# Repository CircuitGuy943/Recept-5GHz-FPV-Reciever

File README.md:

I happened to have a 4.3" TFT display left over from dissassembling my old screen from my Ender 3 and I also had an ongoing project of a flight controller, with FPV functionality and I had an amazing idea, I present to you:

# **Recept!**

Recept is a 5.8GHz video signal reciever board running with an RX5808 as the reciever module and the combined power of an RP2040 and TW8819 decoder chip to quickly decode and output the video signal to a parallel RGB interface (3x8, 40 pin) for a generic 4.3" TFT display. It runs primarilly off of a fully integrated LiPo battery of dimensions and size 903759 / 2500mAh but it also provides the possibily of running off of USB C both for general use or charging the battery automatically using the built in BQ21088 charging chip from TI.

Power the backlight for the display there is an MT3608 24V boost converter paired with another buck/boost converter for the generic 5V rail (LDO wasn't suitable as the RX module power draw is quite high). However for the 1.8V and 3.3V rails, simple LD1117s were used for their low ripple, stable output and low power requirements of the TW8819 and RP2040 ICs. The PCB comes in the preferable dimensions for mounting a generic 4.3" TFT on the back with mounting points for a metal case that also came with my display. It also includes the main power switch (everything but charging) mounted next to the USB C port on the bottom of the board. On the left side you will also find the SMA connector for the 5.8GHz antenna and 8 LEDs, these LEDs are directly controlled by the RP2040 in response to the RSSI signal from the reciever, to give you an easy indication of the signal strength. Besides that there are also several power LEDs and GPIO LED on the other side of the board for general power and functionality debugging in addition to headers near to the SMA connector for more GPIOs/Power/RP2040 debugging. The board also has a keepout zone design to allow double sided tape mounting of the 903759 LiPo battery (on the other side of the display) where it can be easilly soldered to the pads for the battery connection.

There is also a really sleekly designed friction fit case (your mileage may vary with tolerances) designed to house the TFT display and battery mounted on the PCB all in one. It's designed to be easy to print, no supports and pretty much as simple as it gets to assemble. And if that wasn't enough for your preferences of beautiful design, a silkscreen pattern also embosses the board on both sides (although what use this is as you can't even see it in the case, don't ask me) to give a super cool aesthetic.

To use this you simply need the PCB, the display is attached to it using the metal bracket/casing it came in and the battery can either be stuck on with double sided tape or if you're putting it in the case it can even be left loose as it'll be contained. The device then fits into the bottom section of the case and the top section then just simply friction fits over it and sits in place. The configuration code can then bu uploaded using Arduino IDE via the USB C cable onto the RP2040 to configure the TW8819 and allow it to show video on the TFT display.

## Features:
- USB C power supply programming port for the RP2040
- 1s LiPo integration with built in charging
- 4.3" 40 pin TFT display support
- 5.8GHz video band
- Channel switch ability
- RSSI support
- No screw assembly

## PCB
This is the PCB, with L1 to L4 Layers, silkscreen for both layers and an all layers view

And here is the schematic

## Case and 3D renders
Here are also some 3D renders done in fusion to show off the case and it's functionality :)

And last but not least this is a render of the PCB itself:

## Firmware Overview
I've included some basic firmware (**untested**) that should get the TFT display working out of the box with a quick upload from arduino IDE

## BOM:
The BOM list for the actual PCB components is in the BOM folder section and here is also a BOM list for all the other components I plan to buy for this:

- PCB             $198.94		
- Antenna         $7.77      https://www.aliexpress.com/item/1005006153683653.html		
- 90 degree SMA   $4.51      https://www.aliexpress.com/item/1005005665998117.html						
- RX5808 module   $33.54     https://www.ebay.co.uk/itm/264574341923						                (This module is not cheaper on AliExpress)
- Battery         $9.39      https://www.ebay.co.uk/itm/396305473532?var=665862385939						(I don't feel safe buying batteries off Ali)
											
Total			      $246.38

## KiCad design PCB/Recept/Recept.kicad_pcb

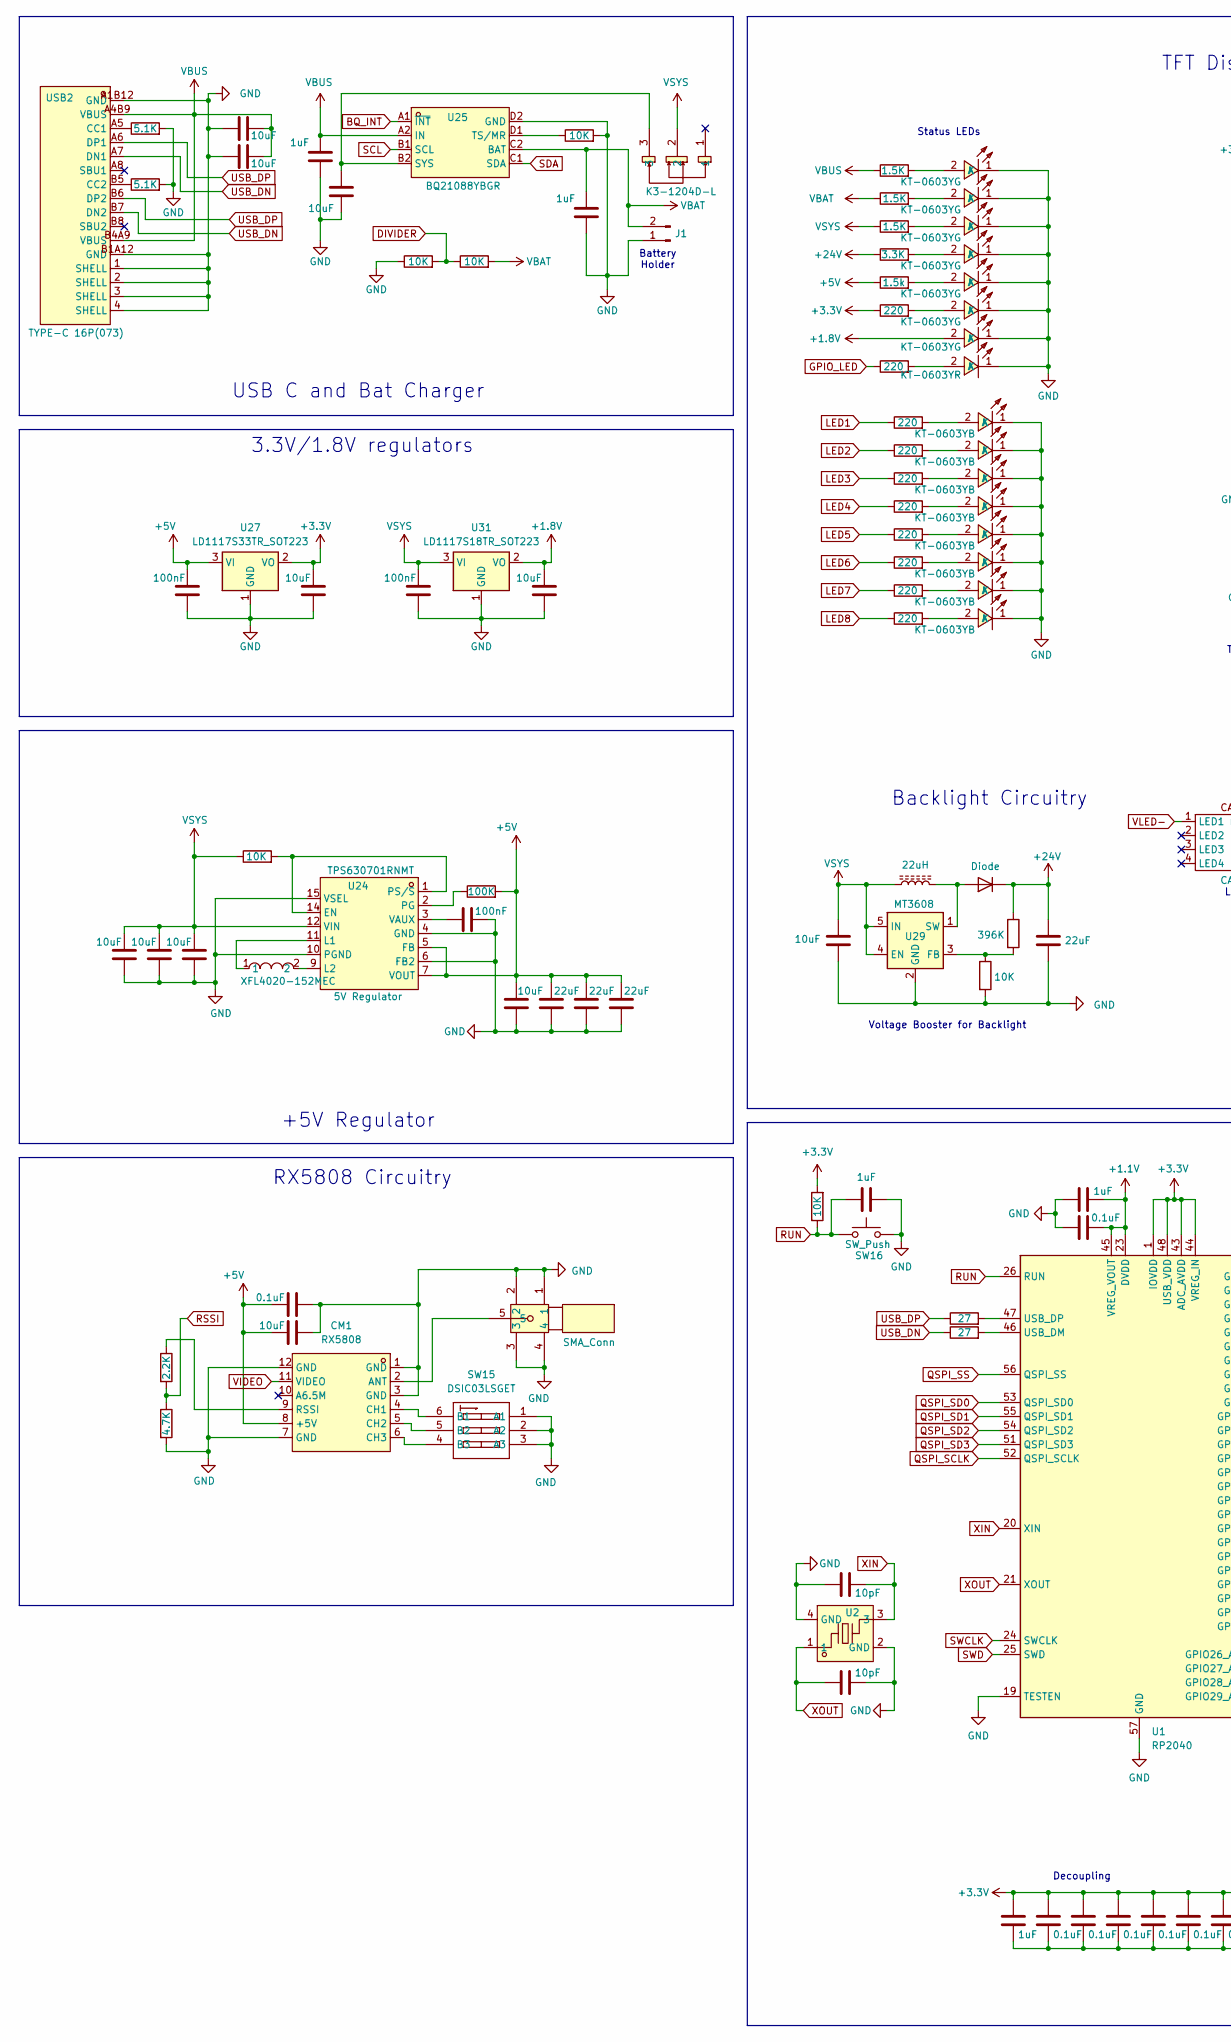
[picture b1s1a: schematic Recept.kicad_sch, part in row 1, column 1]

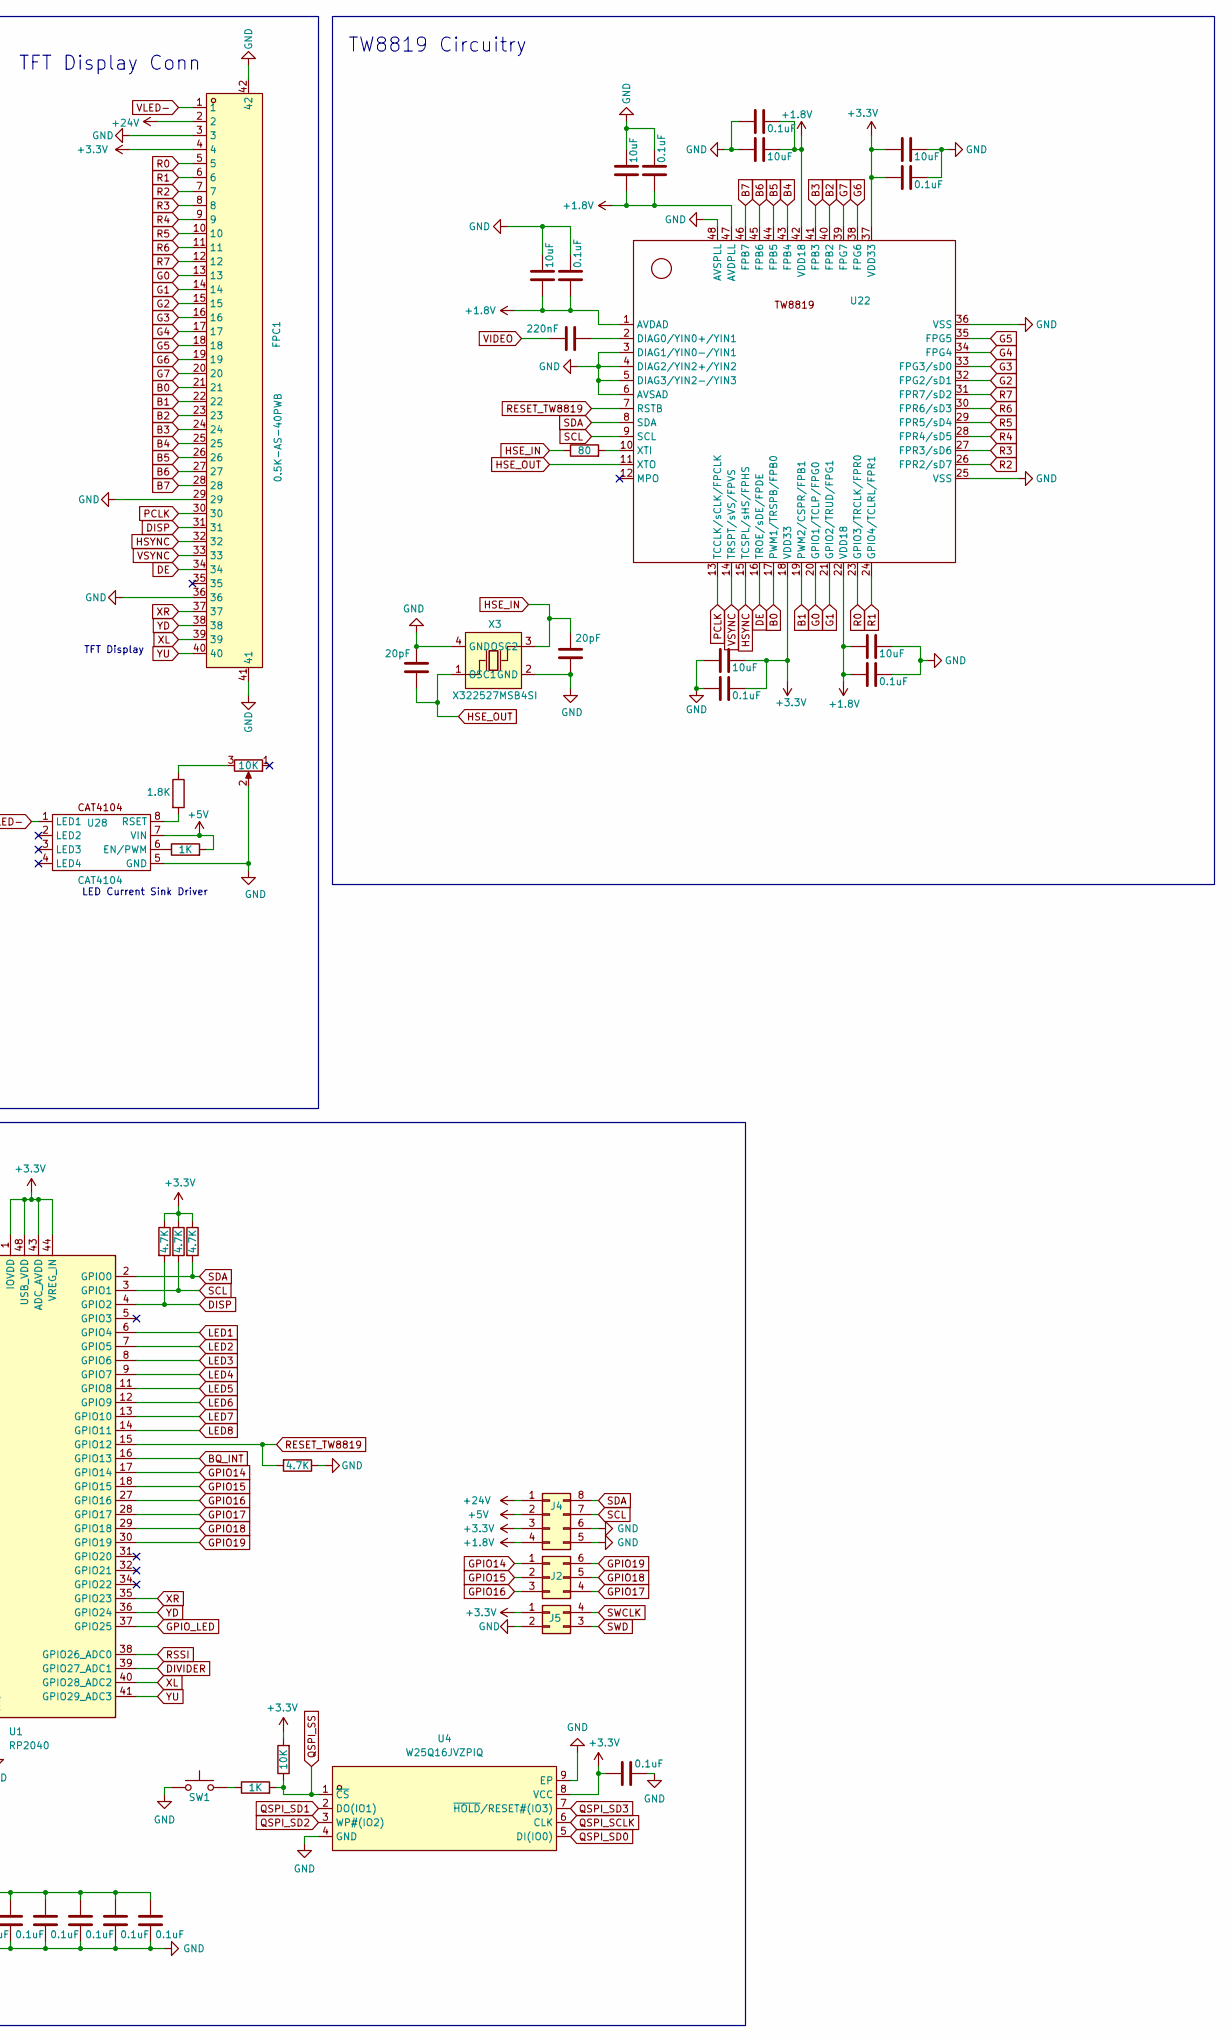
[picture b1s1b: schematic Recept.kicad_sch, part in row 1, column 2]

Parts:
C1, C4, C5, C6, C7, C8, C10, C12, C103, C104, C105, C110, C111, C113, C115, C117, C119: 0.1uF; C_0402_1005Metric
C2, C9: 10pF; C_0402_1005Metric
C3, C96: 1uF; C_0402_1005Metric
C11, C81, C82, C108, C109, C112, C114, C116, C118: 10uF; C_0402_1005Metric
C83, C84: 10uF; C_0805_2012Metric
C85, C87, C92, C94, C97, C100: 10uF; C_0603_1608Metric
C86: 100nF; C_0402_1005Metric
C88, C89, C90: 22uF; C_0805_2012Metric
C91, C93: 100nF; C_0603_1608Metric
C95, C106: 20pF; C_0402_1005Metric
C98: 22uF; C_1206_3216Metric
C99, C101, C102: 1uF; C_0603_1608Metric
C107: 220nF; C_0402_1005Metric
CM1: RX5808; COMM-SMD_12P_RX5808; LCSC Part C2908157
D10: Diode; D_SMB
FPC1: 0.5K-AS-40PWB; FPC-SMD_40P-P0.50_0.5K-AS-40PWB; LCSC Part C2911781
J1: Conn_01x02_Pin; PinHeader_1x02_P2.54mm_Vertical
J2: Conn_02x03_Counter_Clockwise; PinHeader_2x03_P1.27mm_Vertical
J4: Conn_02x04_Counter_Clockwise; PinHeader_2x04_P1.27mm_Vertical
J5: Conn_02x02_Counter_Clockwise; PinHeader_2x02_P1.27mm_Vertical
L3: XFL4020-152MEC; IND-SMD_L4.0-W4.0-A; LCSC Part C3033018
L4: 22uH; IND-SMD_L5.8-W5.8
LED1, LED2, LED3, LED4, LED5, LED6, LED7, LED8: KT-0603YB; LED0603-RD; LCSC Part C2289
LED10, LED17, LED18, LED19, LED20, LED21, LED22: KT-0603YG; LED0603-RD; LCSC Part C2289
LED23: KT-0603YR; LED0603-RD; LCSC Part C2289
R1, R2, R3, R4, R5, R6, R7, R8, R90, R116: 220; R_0402_1005Metric
R9, R10: 27; R_0402_1005Metric
R11, R94: 1K; R_0402_1005Metric
R12, R70, R81, R91, R92, R95, R106: 10K; R_0402_1005Metric
R13, R14, R15, R16, R107: 4.7K; R_0402_1005Metric
R57, R59: 5.1K; R_0402_1005Metric
R71: 100K; R_0402_1005Metric
R79: 80; R_0402_1005Metric
R93: 1.8K; R_0402_1005Metric
R105: 396K; R_0402_1005Metric
R108: 2.2K; R_0402_1005Metric
R111, R112, R113: 1.5K; R_0402_1005Metric
R114: 3.3K; R_0402_1005Metric
R115: 1.5k; R_0402_1005Metric
RV1: 10K; Potentiometer_Bourns_3314J_Vertical
SW1, SW16: SW_Push; SW_Push_1P1T-SH_NO_CK_KMR2xxG
SW15: DSIC03LSGET; SW-SMD_DSIC03LSGET; LCSC Part C57453
SW18: K3-1204D-L; SW-TH_K3-1204D-L; LCSC Part C2909229
U1: RP2040; QFN-56-1EP_7x7mm_P0.4mm_EP3.2x3.2mm
U2: ABM8-272-T3_C20625731; CRYSTAL-SMD_4P-L3.2-W2.5-BL; LCSC Part C20625731
U4: W25Q16JVZPIQ; WSON-8_L6.0-W5.0-P1.27-BL-EP; LCSC Part C377853
U22: QFN-48-1EP_7x7mm_P0.5mm_EP5.6x5.6mm_ThermalVias
U24: TPS630701RNMT; VQFN-15_L3.0-W2.5-P0.50-BL; LCSC Part C181473
U25: BQ21088YBGR; DSBGA-8_L1.5-W1.0-R2-C4-P0.40-BL; LCSC Part C43043519
U27: LD1117S33TR_SOT223; SOT-223-3_TabPin2
U28: CAT4104; SOIC-8_L4.9-W3.9-P1.27-LS6.0-BL
U29: MT3608; SOT-23-6
U30: SMA_Conn; SMA-TH_SMA-KWE_C7498154; LCSC Part C7498154
U31: LD1117S18TR_SOT223; SOT-223-3_TabPin2
USB2: TYPE-C 16P(073); USB-C-SMD_TYPE-C16PIN_C668624; LCSC Part C668624
X3: X322527MSB4SI; CRYSTAL-SMD_4P-L3.2-W2.5-BL-1; LCSC Part C9008

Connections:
+1.1V: C3.1, C8.1, U1.23 (DVDD), U1.45 (VREG_VOUT), U1.50 (DVDD)
+1.8V: C11.2, C12.2, C94.2, C108.1, C111.1, C112.2, C113.2, C116.2, C117.2, J4.4, LED22.2 (A), U22.1 (AVDAD), U22.22 (VDD18), U22.42 (VDD18), U22.47 (AVDPLL), U31.2 (VO)
+3.3V: C1.1, C4.1, C5.1, C6.1, C7.1, C10.2, C92.2, C102.1, C103.1, C104.1, C105.1, C109.2, C110.2, C114.1, C115.1, FPC1.4, J4.3, J5.1, R12.2, R13.1, R14.1, R15.1, R81.2, R116.1, U1.1 (IOVDD), U1.10 (IOVDD), U1.22 (IOVDD), U1.33 (IOVDD), U1.42 (IOVDD), U1.43 (ADC_AVDD), U1.44 (VREG_IN), U1.48 (USB_VDD), U1.49 (IOVDD), U4.8 (VCC), U22.18 (VDD33), U22.37 (VDD33), U27.2 (VO)
+5V: C87.2, C88.2, C89.2, C90.2, C91.2, C118.1, C119.1, CM1.8 (+5V), J4.2, R71.2, R94.2, R115.1, U24.5 (FB), U24.7 (VOUT), U27.3 (VI), U28.7 (VIN)
+24V: C98.2, D10.1 (K), FPC1.2, J4.1, R105.1, R114.1
B0: FPC1.21, U22.17 (PWM1/TRSPB/FPB0)
B1: FPC1.22, U22.19 (PWM2/CSPR/FPB1)
B2: FPC1.23, U22.40 (FPB2)
B3: FPC1.24, U22.41 (FPB3)
B4: FPC1.25, U22.43 (FPB4)
B5: FPC1.26, U22.44 (FPB5)
B6: FPC1.27, U22.45 (FPB6)
B7: FPC1.28, U22.46 (FPB7)
BQ_INT: U1.16 (GPIO13), U25.A1 (~INT)
DE: FPC1.34, U22.16 (TROE/sDE/FPDE)
DISP: FPC1.31, R15.2, U1.4 (GPIO2)
DIVIDER: R91.2, R92.1, U1.39 (GPIO27_ADC1)
G0: FPC1.13, U22.20 (GPIO1/TCLP/FPG0)
G1: FPC1.14, U22.21 (GPIO2/TRUD/FPG1)
G2: FPC1.15, U22.32 (FPG2/sD1)
G3: FPC1.16, U22.33 (FPG3/sD0)
G4: FPC1.17, U22.34 (FPG4)
G5: FPC1.18, U22.35 (FPG5)
G6: FPC1.19, U22.38 (FPG6)
G7: FPC1.20, U22.39 (FPG7)
GND: C1.2, C2.1, C3.2, C4.2, C5.2, C6.2, C7.2, C8.2, C9.2, C10.1, C11.1, C12.1, C81.2, C82.2, C83.1, C84.1, C85.1, C86.2, C87.1, C88.1, C89.1, C90.1, C91.1, C92.1, C93.1, C94.1, C95.1, C96.1, C97.1, C98.1, C99.2, C100.2, C101.2, C102.2, C103.2, C104.2, C105.2, C106.2, C108.2, C109.1, C110.1, C111.2, C112.1, C113.1, C114.2, C115.2, C116.1, C117.1, C118.2, C119.2, CM1.1 (GND), CM1.3 (GND), CM1.7 (GND), CM1.12 (GND), FPC1.3, FPC1.29, FPC1.36, FPC1.41, FPC1.42, J1.1, J4.5, J4.6, J5.2, LED1.1 (K), LED2.1 (K), LED3.1 (K), LED4.1 (K), LED5.1 (K), LED6.1 (K), LED7.1 (K), LED8.1 (K), LED10.1 (K), LED17.1 (K), LED18.1 (K), LED19.1 (K), LED20.1 (K), LED21.1 (K), LED22.1 (K), LED23.1 (K), R16.1, R57.2, R59.2, R91.1, R95.2, R106.2, R107.2, RV1.2, SW1.1, SW15.1 (A1), SW15.2 (A2), SW15.3 (A3), SW16.2, U1.19 (TESTEN), U1.57 (GND), U2.2 (GND), U2.4 (GND), U4.4 (GND), U4.9 (EP), U22.3 (DIAG1/YIN0-/YIN1), U22.4 (DIAG2/YIN2+/YIN2), U22.5 (DIAG3/YIN2-/YIN3), U22.6 (AVSAD), U22.25 (VSS), U22.36 (VSS), U22.48 (AVSPLL), U24.4 (GND), U24.6 (FB2), U24.10 (PGND), U24.15 (VSEL), U25.D2 (GND), U27.1 (GND), U28.5 (GND), U29.2 (GND), U30.1, U30.2, U30.3, U30.4, U31.1 (GND), USB2.1 (SHELL), USB2.2 (SHELL), USB2.3 (SHELL), USB2.4 (SHELL), USB2.A1B12 (GND), USB2.B1A12 (GND), X3.2 (GND), X3.4 (GND)
GPIO14: J2.1, U1.17 (GPIO14)
GPIO15: J2.2, U1.18 (GPIO15)
GPIO16: J2.3, U1.27 (GPIO16)
GPIO17: J2.4, U1.28 (GPIO17)
GPIO18: J2.5, U1.29 (GPIO18)
GPIO19: J2.6, U1.30 (GPIO19)
GPIO_LED: R90.1, U1.37 (GPIO25)
HSE_IN: C106.1, R79.1, X3.3 (OSC2)
HSE_OUT: C95.2, U22.11 (XTO), X3.1 (OSC1)
HSYNC: FPC1.32, U22.15 (TCSPL/sHS/FPHS)
LED1: R1.1, U1.6 (GPIO4)
LED2: R2.1, U1.7 (GPIO5)
LED3: R3.1, U1.8 (GPIO6)
LED4: R4.1, U1.9 (GPIO7)
LED5: R5.1, U1.11 (GPIO8)
LED6: R6.1, U1.12 (GPIO9)
LED7: R7.1, U1.13 (GPIO10)
LED8: R8.1, U1.14 (GPIO11)
unnamed: CM1.2 (ANT), U30.5
unnamed: CM1.4 (CH1), SW15.6 (B1)
unnamed: CM1.5 (CH2), SW15.5 (B2)
unnamed: CM1.6 (CH3), SW15.4 (B3)
unnamed: CM1.9 (RSSI), R108.1
unnamed: D10.2 (A), L4.2, U29.1 (SW)
unnamed: LED1.2 (A), R1.2
unnamed: LED2.2 (A), R2.2
unnamed: LED3.2 (A), R3.2
unnamed: LED4.2 (A), R4.2
unnamed: LED5.2 (A), R5.2
unnamed: LED6.2 (A), R6.2
unnamed: LED7.2 (A), R7.2
unnamed: LED8.2 (A), R8.2
unnamed: LED10.2 (A), R111.2
unnamed: LED17.2 (A), R112.2
unnamed: LED18.2 (A), R113.2
unnamed: LED19.2 (A), R114.2
unnamed: LED20.2 (A), R115.2
unnamed: LED21.2 (A), R116.2
unnamed: LED23.2 (A), R90.2
unnamed: R11.1, SW1.2
unnamed: R93.1, RV1.3
unnamed: R10.2, U1.46 (USB_DM)
unnamed: R9.2, U1.47 (USB_DP)
unnamed: C107.2, U22.2 (DIAG0/YIN0+/YIN1)
unnamed: R79.2, U22.10 (XTI)
unnamed: R70.2, U24.1 (PS/S), U24.14 (EN)
unnamed: L3.1, U24.11 (L1)
unnamed: L3.2, U24.9 (L2)
unnamed: R71.1, U24.2 (PG)
unnamed: C86.1, U24.3 (VAUX)
unnamed: C100.1, SW18.3, U25.B2 (SYS)
unnamed: R106.1, U25.D1 (TS/MR)
unnamed: R94.1, U28.6 (EN/PWM)
unnamed: R93.2, U28.8 (RSET)
unnamed: R95.1, R105.2, U29.3 (FB)
unnamed: R57.1, USB2.A5 (CC1)
unnamed: R59.1, USB2.B5 (CC2)
PCLK: FPC1.30, U22.13 (TCCLK/sCLK/FPCLK)
QSPI_SCLK: U1.52 (QSPI_SCLK), U4.6 (CLK)
QSPI_SD0: U1.53 (QSPI_SD0), U4.5 (DI(IO0))
QSPI_SD1: U1.55 (QSPI_SD1), U4.2 (DO(IO1))
QSPI_SD2: U1.54 (QSPI_SD2), U4.3 (WP#(IO2))
QSPI_SD3: U1.51 (QSPI_SD3), U4.7 (~HOLD/RESET#(IO3))
QSPI_SS: R11.2, R12.1, U1.56 (QSPI_SS), U4.1 (~CS)
R0: FPC1.5, U22.23 (GPIO3/TRCLK/FPR0)
R1: FPC1.6, U22.24 (GPIO4/TCLRL/FPR1)
R2: FPC1.7, U22.26 (FPR2/sD7)
R3: FPC1.8, U22.27 (FPR3/sD6)
R4: FPC1.9, U22.28 (FPR4/sD5)
R5: FPC1.10, U22.29 (FPR5/sD4)
R6: FPC1.11, U22.30 (FPR6/sD3)
R7: FPC1.12, U22.31 (FPR7/sD2)
RESET_TW8819: R16.2, U1.15 (GPIO12), U22.7 (RSTB)
RSSI: R107.1, R108.2, U1.38 (GPIO26_ADC0)
RUN: C96.2, R81.1, SW16.1, U1.26 (RUN)
SCL: J4.7, R14.2, U1.3 (GPIO1), U22.9 (SCL), U25.B1 (SCL)
SDA: J4.8, R13.2, U1.2 (GPIO0), U22.8 (SDA), U25.C1 (SDA)
SWCLK: J5.4, U1.24 (SWCLK)
SWD: J5.3, U1.25 (SWD)
USB_DN: R10.1, USB2.A7 (DN1), USB2.B7 (DN2)
USB_DP: R9.1, USB2.A6 (DP1), USB2.B6 (DP2)
VBAT: C101.1, J1.2, R92.2, R112.1, U25.C2 (BAT)
VBUS: C81.1, C82.1, C99.1, R111.1, U25.A2 (IN), USB2.A4B9 (VBUS), USB2.B4A9 (VBUS)
VIDEO: C107.1, CM1.11 (VIDEO)
VLED-: FPC1.1, U28.1 (LED1)
VSYNC: FPC1.33, U22.14 (TRSPT/sVS/FPVS)
VSYS: C83.2, C84.2, C85.2, C93.2, C97.2, L4.1, R70.1, R113.1, SW18.2, U24.12 (VIN), U29.4 (EN), U29.5 (IN), U31.3 (VI)
XIN: C9.1, U1.20 (XIN), U2.3
XL: FPC1.39, U1.40 (GPIO28_ADC2)
XOUT: C2.2, U1.21 (XOUT), U2.1
XR: FPC1.37, U1.35 (GPIO23)
YD: FPC1.38, U1.36 (GPIO24)
YU: FPC1.40, U1.41 (GPIO29_ADC3)

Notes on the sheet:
Voltage Booster for Backlight
LED Current Sink Driver
TW8819 Circuitry
Decoupling
RX5808 Circuitry
TFT Display
TFT Display Conn
USB C and Bat Charger
3.3V/1.8V regulators
Battery Holder
Backlight Circuitry
Status LEDs
+5V Regulator

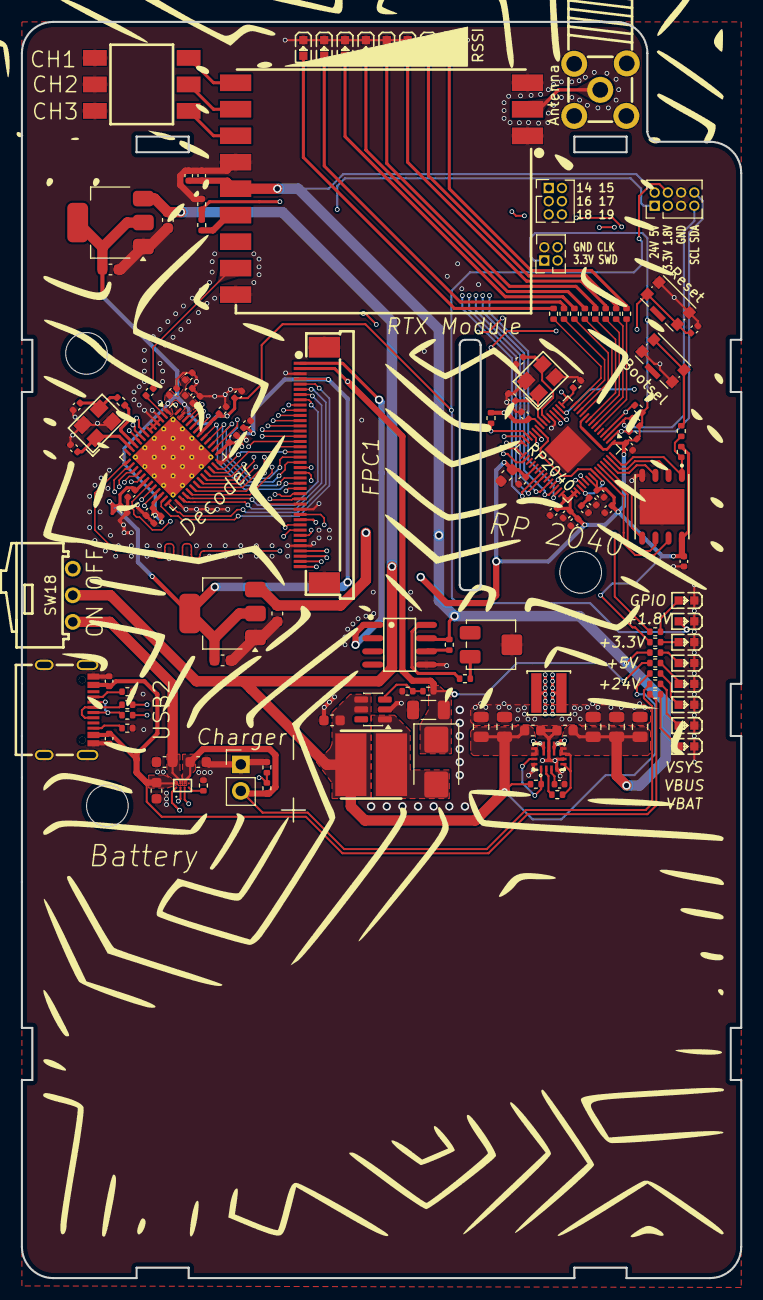
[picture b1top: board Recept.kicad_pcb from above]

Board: 4 copper layers, 69.0 x 120.5 mm, 132 parts (0 on the bottom side), 119 nets.

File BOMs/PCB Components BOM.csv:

Id,Designator,Footprint,Quantity,Designation,Supplier and ref,Column1,_1
1,"R7,R1,R8,R2,R116,R4,R90,R5,R3,R6",R_0402_1005Metric,10,220,,,
2,"LED18,LED20,LED10,LED19,LED17,LED21,LED22",LED0603-RD,7,KT-0603YG,,,
3,"C91,C93",C_0603_1608Metric,2,100nF,,,
4,C99,C_0603_1608Metric,1,4.7uF,,,
5,R93,R_0402_1005Metric,1,1.8K,,,
6,"C5,C113,C6,C111,C8,C7,C12,C103,C117,C10,C115,C104,C105,C110,C4,C1,C119",C_0402_1005Metric,17,0.1uF,,,
7,D10,D_SMB,1,Diode,,,
8,"C94,C87,C85,C92,C97,C101",C_0603_1608Metric,6,10uF,,,
9,"C109,C118,C114,C81,C112,C82,C116,C108,C11",C_0402_1005Metric,9,10uF,,,
10,U28,SOIC-8_L4.9-W3.9-P1.27-LS6.0-BL,1,CAT4104,,,
11,USB2,USB-C-SMD_TYPE-C16PIN_C668624,1,TYPE-C 16P(073),,,
12,"R94,R11",R_0402_1005Metric,2,1K,,,
13,U1,QFN-56-1EP_7x7mm_P0.4mm_EP3.2x3.2mm,1,RP2040,,,
14,"C89,C90,C88",C_0805_2012Metric,3,22uF,,,
15,"R70,R81,R106,R92,R95,R91,R12",R_0402_1005Metric,7,10K,,,
16,R105,R_0402_1005Metric,1,396K,,,
17,U25,DSBGA-8_L1.5-W1.0-R2-C4-P0.40-BL,1,BQ21088YBGR,,,
18,"R57,R59",R_0402_1005Metric,2,5.1K,,,
19,C98,C_0603_1608Metric,1,22uF,,,
20,J1,PinHeader_1x02_P2.54mm_Vertical,1,Conn_01x02_Pin,,,
21,"R14,R15,R107,R16,R13",R_0402_1005Metric,5,4.7K,,,
22,R71,R_0402_1005Metric,1,100K,,,
23,U22,QFN-48-1EP_7x7mm_P0.5mm_EP5.6x5.6mm_ThermalVias,1,~,,,
24,FPC1,FPC-SMD_40P-P0.50_0.5K-AS-40PWB,1,0.5K-AS-40PWB,,,
25,"C106,C95",C_0402_1005Metric,2,20pF,,,
26,"C96,C3",C_0402_1005Metric,2,1uF,,,
27,C100,C_0603_1608Metric,1,33uF,,,
28,"SW1,SW16",SW_Push_1P1T-SH_NO_CK_KMR2xxG,2,SW_Push,,,
29,"R111,R113,R112",R_0402_1005Metric,3,1.5K,,,
30,X3,CRYSTAL-SMD_4P-L3.2-W2.5-BL-1,1,X322527MSB4SI,,,
31,"C84,C83",C_0805_2012Metric,2,10uF,,,
32,C86,C_0402_1005Metric,1,100nF,,,
33,"LED8,LED7,LED2,LED5,LED3,LED1,LED6,LED4",LED0603-RD,8,KT-0603YB,,,
34,J5,PinHeader_2x02_P1.27mm_Vertical,1,Conn_02x02_Counter_Clockwise,,,
35,SW18,SW-TH_K3-1204D-L,1,K3-1204D-L,,,
36,C102,C_0603_1608Metric,1,1uF,,,
37,U31,SOT-223-3_TabPin2,1,LD1117S18TR_SOT223,,,
38,U29,SOT-23-6,1,MT3608,,,
39,R114,R_0402_1005Metric,1,3.3K,,,
40,U24,VQFN-15_L3.0-W2.5-P0.50-BL,1,TPS630701RNMT,,,
41,U2,CRYSTAL-SMD_4P-L3.2-W2.5-BL,1,ABM8-272-T3_C20625731,,,
42,RV1,Potentiometer_Bourns_3314J_Vertical,1,10K,,,
43,"R10,R9",R_0402_1005Metric,2,27,,,
44,U30,SMA-TH_SMA-KWE_C7498154,1,SMA_Conn,,,
45,U27,SOT-223-3_TabPin2,1,LD1117S33TR_SOT223,,,
46,L4,IND-SMD_L5.8-W5.8,1,22uH,,,
47,C107,C_0402_1005Metric,1,220nF,,,
48,"C2,C9",C_0402_1005Metric,2,10pF,,,
49,CM1,COMM-SMD_12P_RX5808,1,RX5808,,,
50,R108,R_0402_1005Metric,1,2.2K,,,
51,J4,PinHeader_2x04_P1.27mm_Vertical,1,Conn_02x04_Counter_Clockwise,,,
52,U4,WSON-8_L6.0-W5.0-P1.27-BL-EP,1,W25Q16JVZPIQ,,,
53,L3,IND-SMD_L4.0-W4.0-A,1,XFL4020-152MEC,,,
54,R79,R_0402_1005Metric,1,80,,,
55,J2,PinHeader_2x03_P1.27mm_Vertical,1,Conn_02x03_Counter_Clockwise,,,
56,SW15,SW-SMD_DSIC03LSGET,1,DSIC03LSGET,,,
57,LED23,LED0603-RD,1,KT-0603YR,,,
58,R115,R_0402_1005Metric,1,1.5k,,,

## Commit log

2026-03-08 Add PCB
2026-03-23 Revise README with project details and BOM
    Expanded the README to include detailed project description, features, PCB design, firmware overview, and BOM list.
2026-03-25 firmware
